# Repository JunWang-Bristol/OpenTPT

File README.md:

# OpenTPT - Open Triple Pulse Test

OpenTPT is an open-source Triple Pulse Test (TPT) platform for magnetic characterization of core loss and inductance in power magnetics and power electronics applications.

**📄 Paper:** [Triple Pulse Test (TPT) for Characterizing Magnetic Components](https://research-information.bris.ac.uk/en/publications/triple-pulse-test-tpt-for-characterizing-power-loss-in-magnetic-c)

---

## 📋 Overview

The **Triple Pulse Test (TPT)** is a discontinuous excitation method for characterizing power losses and inductance in magnetic components. Unlike traditional continuous excitation methods, TPT uses a series of precisely timed pulses to achieve steady-state magnetic conditions rapidly.

### Discontinuous Procedure

| Pulse | Purpose | Description |
|-------|---------|-------------|
| **First Pulse** | Establish DC bias | No additional DC bias source needed |
| **Second Pulse(s)** | Stabilizing | Allow transients to settle |
| **Third Pulse** | Target cycle | Steady-state measurement |

---

## ✨ Features

- ⚡ **Rapid Testing** – Short transition time (100–500 µs), ideal for end-of-line and 100% testing
- 🔄 **Bidirectional Current Flow** – Emulates practical B-H loop in PWM converters
- 💰 **Low Cost** – Reduced setup requirements compared to traditional methods
- 🌡️ **Constant Temperature** – Negligible heat generated during testing
- 📊 **DC Bias Capability** – Characterize saturation curves with built-in DC bias support
- 🖥️ **Web Dashboard** – Real-time visualization with Dash frontend

---

## 🔧 Hardware Setup

### Testing Circuit (Half-Bridge)

### Example Equipment

| Component | Supported Models | Description |
|-----------|-----------------|-------------|
| **Power Supply** | BK Precision 9129B | Dual-channel supply (V+ and V-) |
| **Oscilloscope** | PicoScope 2408B | Captures voltage/current waveforms |
| **Control Board** | NUCLEO-H503RB, ST2402 | Generates PWM pulses for H-bridge |
| **Current Probe** | 100 mV/A (recommended) | Measures inductor current, > 20 MHz |
| **Voltage Probes** | 10:1 passive probes | Input/output voltage measurement |

> 💡 **Use Your Existing Equipment!**
>
> TPT is designed to work with lab equipment you likely already have. The modular architecture uses a **`hardware_configuration.json`** file to specify your power supply, oscilloscope, and control board. Simply configure the JSON with your device names and COM ports—no need to purchase specific models listed above.
>
> Adding support for new hardware is straightforward: implement the interfaces in `power_supply.py`, `oscilloscope.py`, or `board.py`.

---

## 🚀 Quick Start

### Prerequisites

- Python 3.8 or higher
- Hardware setup (power supply, oscilloscope, control board) connected to your PC

### Installation

1. **Clone the repository**
   ```bash
   git clone https://github.com/JunWang-Bristol/OpenTPT.git
   cd OpenTPT
   ```

2. **Create a virtual environment** (recommended)
   ```bash
   python -m venv venv
   
   # Windows
   venv\Scripts\activate
   
   # Linux/macOS
   source venv/bin/activate
   ```

3. **Install dependencies**
   ```bash
   pip install -r requirements.txt
   ```

4. **Configure hardware** – Copy and edit the hardware configuration:
   ```bash
   cp hardware_configuration_template.json hardware_configuration.json
   ```
   
   Edit `hardware_configuration.json` with your port assignments:
   ```json
   {
       "power_supply": "BK9129B",
       "power_supply_port": "COM3",
       "oscilloscope": "PicoScope2408B",
       "oscilloscope_port": "COM5",
       "board": "NUCLEO-H503RB",
       "board_port": "COM6",
       "input_voltage_probe_scale": 10,
       "output_voltage_probe_scale": 10,
       "current_probe_scale": 10
   }
   ```

5. **Verify your setup** – Run tests to ensure everything is configured correctly:
   ```bash
   cd tests
   python -m pytest .
   ```
   
   Or run individual hardware tests:
   ```bash
   python board_tests.py
   python oscilloscope_tests.py
   python power_supply_tests.py
   ```

### Running Your First Measurement

#### Using Python API

```python
from src.tpt import InductanceMeasurement, CoreLossesMeasurement

# Initialize the measurement system
meas = InductanceMeasurement(
    power_supply='BK9129B',
    oscilloscope='PicoScope2408B',
    board='NUCLEO-H503RB',
    power_supply_port='COM3',
    oscilloscope_port='USB',
    board_port='COM6',
    current_probe_scale=10   # 100 mV/A probe (10 A/V)
)

# Demagnetize the core before measurement
meas.demagnetize()

# Create test parameters for frequency sweep
params = meas.create_balanced_pulse_train(
    voltage=10,       # Voltage amplitude (V)
    frequency=100000, # Frequency (Hz)
    num_pulses=4      # Number of pulse pairs
)

# Run measurement...
# (See examples in documentation)

# Clean up after measurement
meas.demagnetize()
```

#### Using Web Dashboard

1. Navigate to the frontend directory:
   ```bash
   cd src/frontend
   ```

2. Run the dashboard:
   ```bash
   python frontend.py
   ```

3. Open your browser to `http://127.0.0.1:8050`

---

## 📁 Project Structure

```
OpenTPT/
├── src/
│   ├── tpt.py                 # Main measurement classes (InductanceMeasurement, CoreLossesMeasurement)
│   ├── post_processor.py      # Waveform analysis and loop extraction
│   ├── board.py               # Control board interface
│   ├── oscilloscope.py        # Oscilloscope interface
│   ├── power_supply.py        # Power supply interface
│   ├── boards/                # Board drivers
│   │   ├── NUCLEO-H503RB/     # STM32 NUCLEO board firmware
│   │   └── ST2402/            # ST2402 driver board support
│   ├── oscilloscopes/         # Oscilloscope drivers
│   │   └── PicoScope.py       # PicoScope 2408B driver
│   ├── power_supplies/        # Power supply drivers
│   │   └── BK.py              # BK Precision 9129B driver
│   └── frontend/              # Web dashboard
│       └── frontend.py        # Dash-based GUI
├── tests/                     # Unit tests
├── hardware_configuration_template.json
├── requirements.txt
└── LICENSE
```

---

## 📝 Configuration Notes

### Current Probe Scale

> ⚠️ **Important:** The `current_probe_scale` defines how to convert oscilloscope voltage readings to actual current values:
>
> `Current (A) = Oscilloscope Voltage (V) × probe_scale`
>
> `probe_scale` must be entered in **A/V** — the reciprocal of the probe's rated sensitivity
> (often printed as mV/A, V/A, or as a current-probe amplifier's "mA/mV" gain setting).

| Probe Sensitivity | Probe Scale Value |
|-------------------|-------------------|
| 100 mV/A (0.1 V/A) | `10` |
| 1 V/A | `1.0` |
| 10 mV/A (0.01 V/A) | `100` |

**Common mistake:** For a 100 mV/A probe, use `scale=10` (not 0.1). The probe outputs 0.1 V when 1 A flows, so you must *divide* by 0.1 (i.e. multiply by 10) to recover amperes. Using the raw 0.1 V/A rating directly under-reports current by 100x — if a Tektronix P6021-style current-probe amplifier is set to "10 mA/mV", that dial reading is already in A/V and can be entered as `scale=10` with no conversion.

---

## 🤝 Contributors

| Organization | Contributors |
|-------------|--------------|
| **PSMA/Würth Elektronik** | George Slama, Alfonso Martinez, Matt Wilkowski |
| **University of Bristol** | Jun Wang, Binyu Cui, Jingrong Yang |
| **University of Manchester** | Cheng Zhang |

---

## 📅 Roadmap

**🚧 OpenTPT – Project Under Construction**

Expected release: **APEC 2027**

---

## 📄 License

This project is licensed under the **BSD 4-Clause License** – see the [LICENSE](LICENSE) file for details.

Copyright © 2023, University of Bristol

---

## 📚 Citation

If you use this project in your research, please cite:

```bibtex
@inproceedings{OpenTPT,
  title={Triple Pulse Test (TPT) for characterizing power loss in magnetic components in analogous to Double Pulse Test (DPT) for power electronics devices},
  author={Wang, Jun and others},
  booktitle={IEEE Proc. Annual Conference of the IEEE Industrial Electronics Society (IECON)},
  year={2020}
}
```

---

## 📧 Contact

For questions, issues, or contributions, please:
- Open an [issue](https://github.com/JunWang-Bristol/OpenTPT/issues) on GitHub
- Contact the team at jun.wang@bristol.ac.uk

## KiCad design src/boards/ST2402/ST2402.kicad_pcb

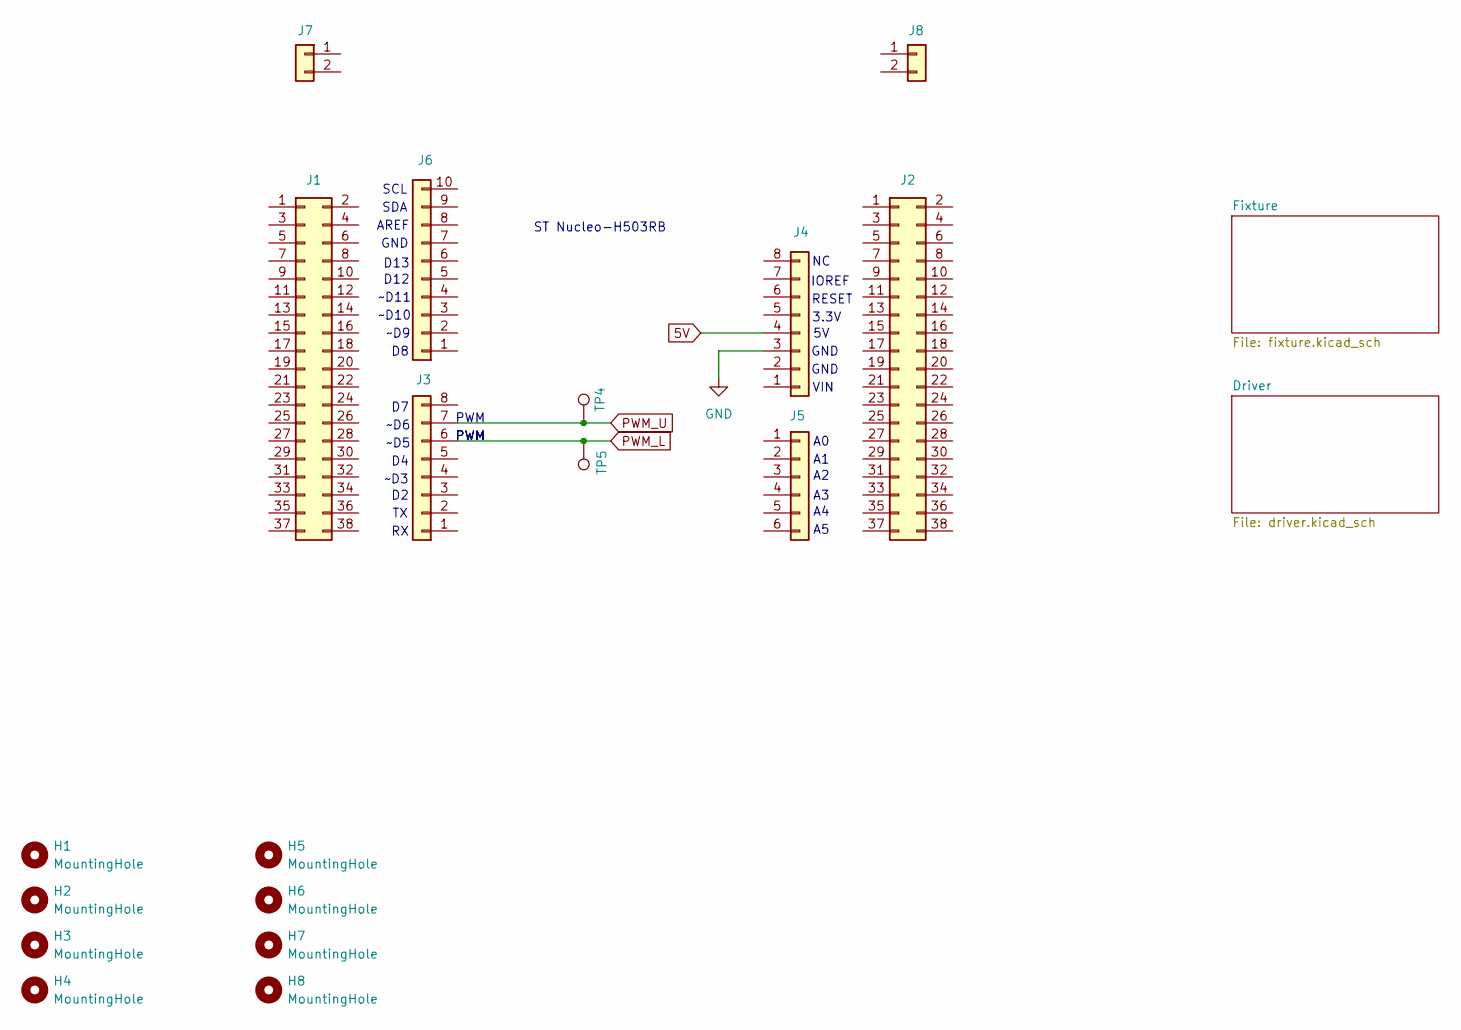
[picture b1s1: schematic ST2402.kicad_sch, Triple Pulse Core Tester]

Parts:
H1, H2, H3, H4, H5, H6, H7, H8: MountingHole; MountingHole_3.2mm_M3_DIN965
J1, J2: Conn_02x19_Odd_Even; PinHeader_2x19_P2.54mm_Vertical
J3, J4: Conn_01x08; PinHeader_1x08_P2.54mm_Vertical
J5: Conn_01x06; PinHeader_1x06_P2.54mm_Vertical
J6: Conn_01x10; PinHeader_1x10_P2.54mm_Vertical
J7, J8: Conn_01x02; PinHeader_1x02_P2.54mm_Vertical
TP4, TP5: TestPoint; TestPoint_Keystone_5010-5014_Multipurpose

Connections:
5V: J4.4
GND: J4.3; also elsewhere on the board
PWM_L: J3.6, TP5.1; also elsewhere on the board
PWM_U: J3.7, TP4.1; also elsewhere on the board

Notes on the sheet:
~D9
GND
3.3V
SCL
IOREF
SDA
D13
RESET
~D11
~D6
PWM
D12
~D5
~D3
AREF
VIN
~D10
ST Nucleo-H503RB

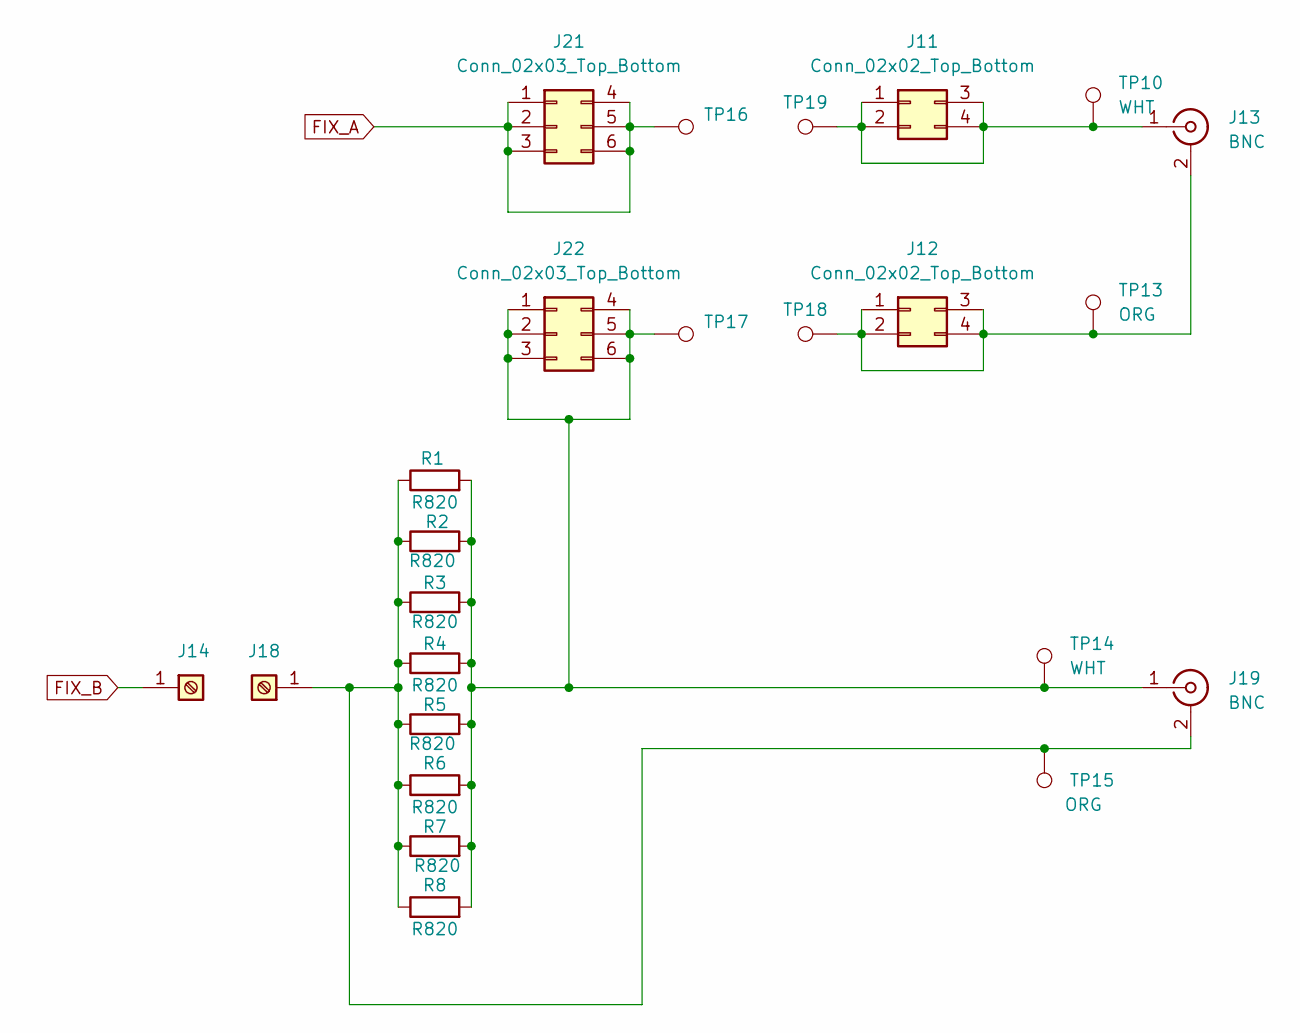
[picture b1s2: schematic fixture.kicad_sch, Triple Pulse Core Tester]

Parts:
J11, J12: Conn_02x02_Top_Bottom; PinSocket_2x02_P2.54mm_Vertical
J13, J19: BNC; BNC_Amphenol_B6252HB-NPP3G-50_Horizontal
J14, J18: Screw_Terminal_01x01; TestPoint_Plated_Hole_D2.0mm
J21, J22: Conn_02x03_Top_Bottom; PinHeader_2x03_P2.54mm_Vertical
R1, R2, R3, R4, R5, R6, R7, R8: R820; R_0805_2012Metric
TP10, TP14: WHT; TestPoint_THTPad_D2.0mm_Drill1.0mm
TP13, TP15: ORG; TestPoint_THTPad_D2.0mm_Drill1.0mm
TP16, TP17, TP18, TP19: TestPoint; TestPoint_Plated_Hole_D5.0mm

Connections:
FIX_A: J21.1, J21.2, J21.3, J21.4, J21.5, J21.6, TP16.1; also elsewhere on the board
FIX_B: J14.1; also elsewhere on the board
unnamed: J11.1, J11.2, J11.3, J11.4, J13.1 (In), TP10.1, TP19.1
unnamed: J12.1, J12.2, J12.3, J12.4, J13.2 (Ext), TP13.1, TP18.1
unnamed: J18.1, J19.2 (Ext), R1.1, R2.1, R3.1, R4.1, R5.1, R6.1, R7.1, R8.1, TP15.1
unnamed 11: J19.1 (In), J22.1, J22.2, J22.3, J22.4, J22.5, J22.6, R1.2, R2.2, R3.2, R4.2, R5.2, R6.2, R7.2, R8.2, TP14.1, TP17.1; also elsewhere on the board

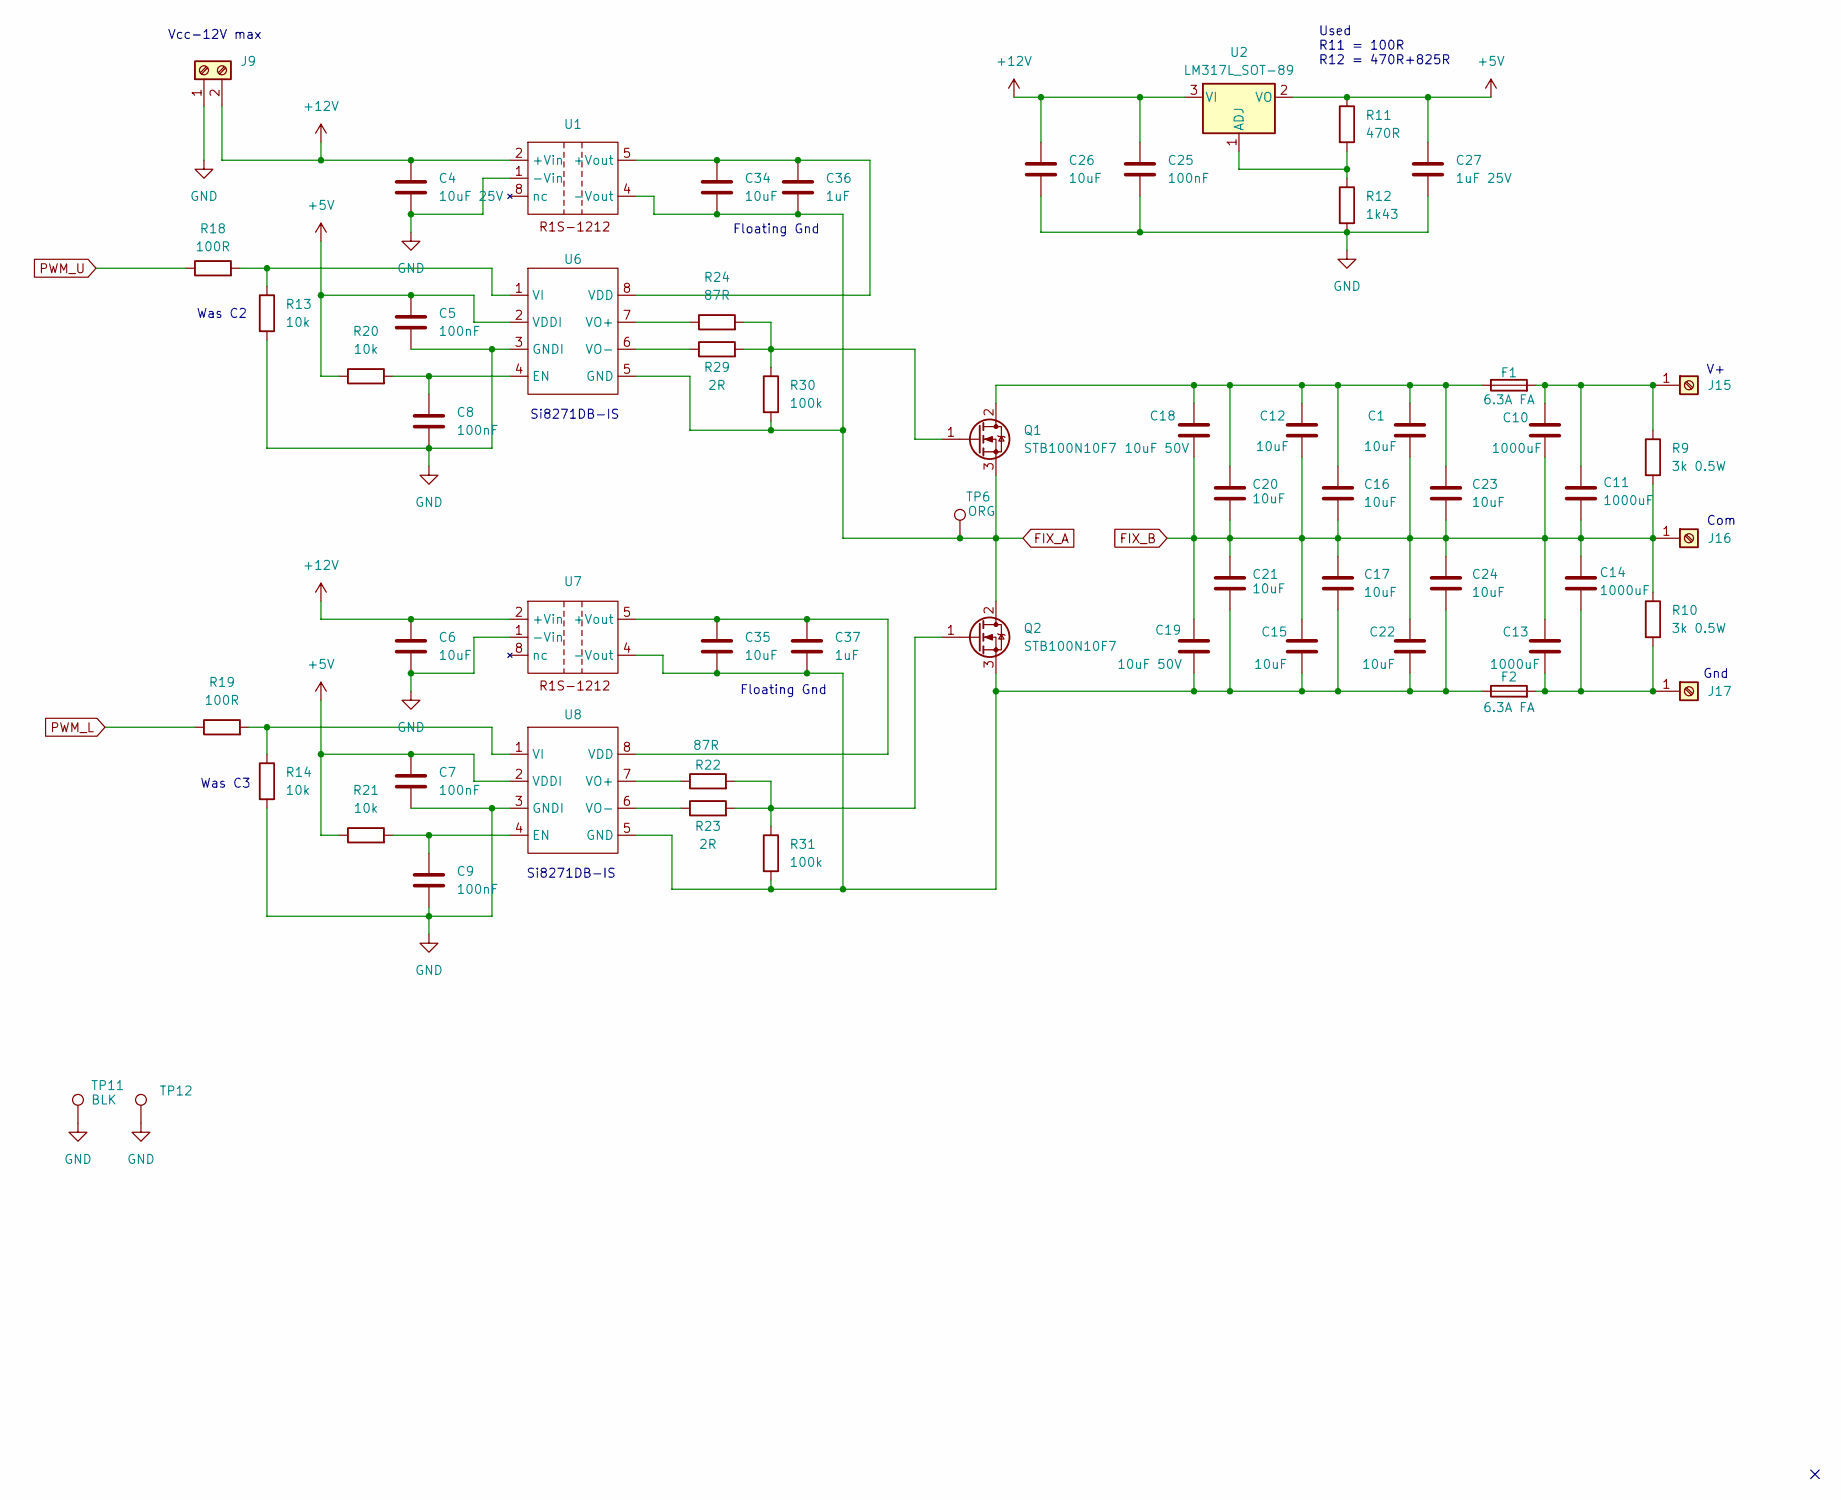
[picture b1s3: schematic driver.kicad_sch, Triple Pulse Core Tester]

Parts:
C1, C12, C15, C16, C17, C20, C21, C22, C23, C24: 10uF; C_1210_3225Metric
C4: 10uF 25V; C_0805_2012Metric
C5, C7, C8, C9, C25: 100nF; C_0805_2012Metric
C6, C26, C34, C35: 10uF; C_0805_2012Metric
C10, C11, C13, C14: 1000uF; CP_Radial_D30.0mm_P10.00mm_SnapIn
C18, C19: 10uF 50V; C_1210_3225Metric
C27: 1uF 25V; C_0805_2012Metric
C36, C37: 1uF; C_0805_2012Metric
F1, F2: 6.3A FA; Fuseholder_TR5_Littelfuse_No560_No460
J9: Screw_Terminal_01x02; TerminalBlock_bornier-2_P5.08mm
J15, J16, J17: Screw_Terminal_01x01; Banana_4mm_pcb
Q1, Q2: STB100N10F7; TO-220-3_Vertical
R9, R10: 3k 0.5W; R_Axial_DIN0309_L9.0mm_D3.2mm_P15.24mm_Horizontal
R11: 470R; R_0805_2012Metric
R12: 1k43; R_0805_2012Metric
R13, R14, R20, R21: 10k; R_0805_2012Metric
R18, R19: 100R; R_0805_2012Metric
R22, R24: 87R; R_0805_2012Metric
R23, R29: 2R; R_0805_2012Metric
R30, R31: 100k; R_0805_2012Metric
TP6: ORG; TestPoint_Keystone_5010-5014_Multipurpose
TP11: BLK; TestPoint_Keystone_5010-5014_Multipurpose
TP12: TestPoint; TestPoint_Keystone_5010-5014_Multipurpose
U1, U7: 5_pin_single_smd
U2: LM317L_SOT-89; SOT-89-3
U6, U8: SOIC-8_3.9x4.9mm_P1.27mm

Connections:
+5V: C5.1, C7.1, C27.1, R11.1, R20.1, R21.1, U2.2 (VO), U6.2 (VDDI), U8.2 (VDDI)
+12V: C4.1, C6.1, C25.1, C26.1, J9.2, U1.2 (+Vin), U2.3 (VI), U7.2 (+Vin)
FIX_A: C34.2, C36.2, Q1.3 (S), Q2.2 (D), R30.2, TP6.1, U1.4 (-Vout), U6.5 (GND); also elsewhere on the board
FIX_B: C1.2, C10.2, C11.2, C12.2, C13.1, C14.1, C15.1, C16.2, C17.1, C18.2, C19.1, C20.2, C21.1, C22.1, C23.2, C24.1, J16.1, R9.2, R10.1; also elsewhere on the board
GND: C4.2, C5.2, C6.2, C7.2, C8.2, C9.2, C25.2, C26.2, C27.2, J9.1, R12.2, R13.2, R14.2, TP11.1, TP12.1, U1.1 (-Vin), U6.3 (GNDI), U7.1 (-Vin), U8.3 (GNDI); also elsewhere on the board
unnamed: C10.1, C11.1, F1.2, J15.1, R9.1
unnamed: C13.2, C14.2, F2.2, J17.1, R10.2
unnamed: C1.1, C12.1, C16.1, C18.1, C20.1, C23.1, F1.1, Q1.2 (D)
unnamed: Q1.1 (G), R24.2, R29.2, R30.1
unnamed: Q2.1 (G), R22.2, R23.2, R31.1
unnamed: C15.2, C17.2, C19.2, C21.2, C22.2, C24.2, C35.2, C37.2, F2.1, Q2.3 (S), R31.2, U7.4 (-Vout), U8.5 (GND)
unnamed: C34.1, C36.1, U1.5 (+Vout), U6.8 (VDD)
unnamed: R11.2, R12.1, U2.1 (ADJ)
unnamed: C8.1, R20.2, U6.4 (EN)
unnamed 19: R13.1, R18.2, U6.1 (VI); also elsewhere on the board
unnamed: R24.1, U6.7 (VO+)
unnamed: R29.1, U6.6 (VO-)
unnamed: C35.1, C37.1, U7.5 (+Vout), U8.8 (VDD)
unnamed: C9.1, R21.2, U8.4 (EN)
unnamed 24: R14.1, R19.2, U8.1 (VI); also elsewhere on the board
unnamed: R22.1, U8.7 (VO+)
unnamed: R23.1, U8.6 (VO-)
PWM_L: R19.1; also elsewhere on the board
PWM_U: R18.1; also elsewhere on the board

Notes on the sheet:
Was C3
Si8271DB-IS
Was C2
Vcc-12V max
Floating Gnd
Used R11 = 100R R12 = 470R+825R
Gnd
Com

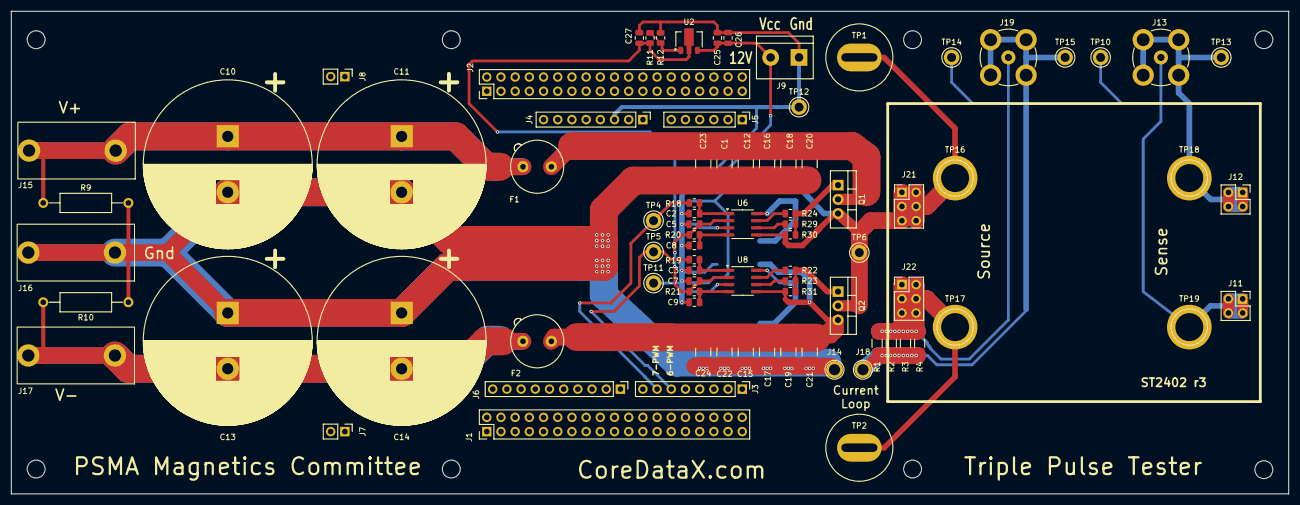
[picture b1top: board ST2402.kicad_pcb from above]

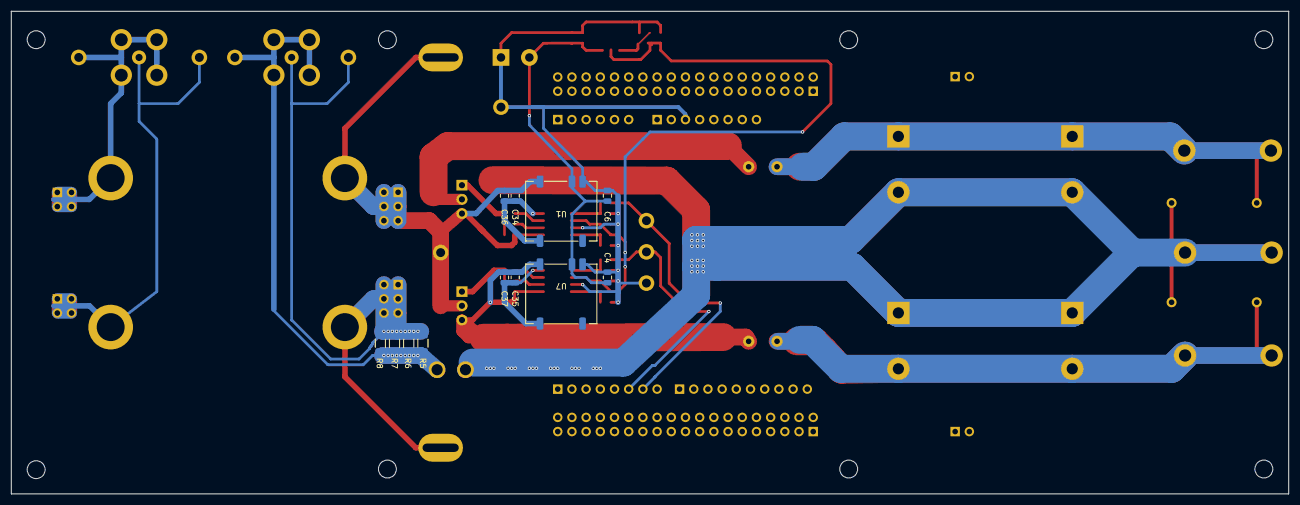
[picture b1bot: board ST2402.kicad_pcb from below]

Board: 2 copper layers, 228.6 x 86.4 mm, 105 parts (12 on the bottom side), 28 nets.

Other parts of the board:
C2, C3: 100nF; C_0805_2012Metric
TP1, TP2: TestPoint; TestPoint_Plated_Hole_D5.0mm

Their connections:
FIX_A: TP1.1; also elsewhere on the board
GND: C2.2, C3.2; also elsewhere on the board
unnamed 11: TP2.1; also elsewhere on the board
unnamed 19: C2.1; also elsewhere on the board
unnamed 24: C3.1; also elsewhere on the board

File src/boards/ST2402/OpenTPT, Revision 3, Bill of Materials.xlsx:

Index | Reference | Value | Footprint | Mfg / Part Number | Replacement Part | Qty Per Assembly | Mouser SKU (ref) | DKPN | DK, Qty Price Break | Price Each | Qty x3+10%+Break | Expan Cost | Notes
1 | U1,U7 | R1S-1212 | GS_Library:5_pin_single_smd |  |  | 2 | 919-R1S-1212 | 945-3298-ND | 1 | 7.75 | 7 | 54.25
2 | U2 | LM317L_SOT-89 | Package_TO_SOT_SMD:SOT-89-3 | LM317LCPK |  | 1 | 595-LM317LCPK | 296-26093-1-ND | 10 | 0.437 | 10 | 4.37
3 | U6,U8 | Si8271DB-IS | Package_SO:SOIC-8_3.9x4.9mm_P1.27mm | Si8271DB-IS |  | 2 | 634-Si8271DB-IS | 336-3532-5-ND | 10 | 2.677 | 10 | 26.77
4 | Q1,Q2 | STP100N10F7 | Package_TO_SOT_THT:TO-220-3_Vertical | STP100N10F7 |  | 2 | 511-STP100N10F7 | 497-13550-5-ND | 1 | 0.269 | 7 | 1.883 | Schematic calls for STB100N10F7, this is D2PAK part. PCB has TO-220 parts.
5 | C5,C7,C8,C9,C25 | 100 nF, 16 V | Capacitor_SMD:C_0805_2012Metric | 885012207098 |  | 5 | 710-885012207098 | 732-8080-1-ND | 10 | 0.038 | 20 | 0.76
6 | C27,C36,C37 | 1 uF, 25V | Capacitor_SMD:C_0805_2012Metric | 885012207103 |  | 3 | 710-85012207103 | 732-7678-1-ND | 10 | 0.169 | 10 | 1.69
7 | C4, C6,C26,C34,C35 | 10 uF, 25V | Capacitor_SMD:C_0805_2012Metric | GRM21BR61H106KE43L |  | 5 |  | 490-18663-1-ND | 10 | 0.174 | 20 | 3.48
8 | C1,C12,C15,C16,C17,C18,C19,C20,C21,C22,C23,C24 | 10 uF, 50 V, X7R | Capacitor_SMD:C_1210_3225Metric | Wurth 885012209073 | CL32B106KBJNNNE | 12 | 710-885012209073 | 1276-3387-1-ND | 10 | 0.35 | 40 | 14
9 | C10,C11,C13,C14 | 1000 uF, 200 V | Capacitor_THT:CP_Radial_D30.0mm_P10.00mm_SnapIn | Wurth 861141085021 |  | 4 | 710-861141085021 | 732-11901-ND | 10 | 5.14 | 20 | 102.8
10 | R23,R29 | 2 ohm | Resistor_SMD:R_0805_2012Metric | CRCW08052R00FKEA |  | 2 | 71-RCW08052R00FKEA | 541-2.00CCCT-ND | 10 | 0.05 | 10 | 0.5
11 | R22,R24 | 87 ohm, 1% | Resistor_SMD:R_0805_2012Metric |  | ERJ-6ENF86R6V | 2 |  | P86.6CCT-ND | 10 | 0.052 | 10 | 0.52 | ls off
12 | R18,R19 | 100 ohm, 1% | Resistor_SMD:R_0805_2012Metric |  | ERJ-P06F1000V | 2 |  | P16057CT-ND | 10 | 0.084 | 10 | 0.84 | dead time
13 | R11 | 470 ohm | Resistor_SMD:R_0805_2012Metric | RC0805FR-07470RL |  | 1 | 603-RC0805FR-07470RL | 311-470CRCT-ND | 10 | 0.012 | 10 | 0.12
14 | R1,R2,R3,R4,R5,R6,R7,R8 | R820, 1%, 1206, 100ppm | Resistor_SMD:R_1206_3216Metric | RCWE1206R820FKEA |  | 8 | 71-RCWE1206R820FKEA | RCWE.82ECT-ND | 10 | 0.179 | 30 | 5.37
15 | (Alt for R1,R2,R3,R4,R5,R6,R7,R8) | R820, 1%, 1206, 200ppm | Resistor_SMD:R_1206_3216Metric | ERJ-8BQFR82V |  | 8 | 667-ERJ-8BQFR82V
16 | R12 | 1.43k ohm | Resistor_SMD:R_0805_2012Metric |  | CRCW08051K43FKEA | 1 |  | 541-1.43KCCT-ND | 10 | 0.041 | 10 | 0.41
17 | R9,R10 | 3k 0.5W | Resistor_THT:R_Axial_DIN0309_L9.0mm_D3.2mm_P15.24mm_Horizontal | RSF100JB-73-3K |  | 2 | 603-RSF100JB-73-3K | 3.0KW-1-ND | 10 | 0.119 | 10 | 1.19 | Part specs are larger than PCB footprint, but values are correct. Float part fo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
18 | R13,R14,R20,R21 | 10k ohm, 1% | Resistor_SMD:R_0805_2012Metric |  | ERJ-6ENF1002V | 4 |  | P10.0KCCT-ND | 10 | 0.052 | 20 | 1.04 | hs off, enable pins
19 | R30,R31 | 100k ohm | Resistor_SMD:R_0805_2012Metric | RC0805FR-07100KL |  | 2 | 603-RC0805FR-07100KL | 311-100KCRCT-ND | 10 | 0.01 | 10 | 0.1
20 | F1,F2 | 6.3A FA | Fuse:Fuseholder_TR5_Littelfuse_No560_No460 | Littelfuse 37316300410 |  | 2 | 576-37316300410 | WK3066BK-ND | 10 | 1.27 | 10 | 12.7
21 | (Also for F1, F2) | Fuse holder |  | Littelfuse #560, 6.3A | 56000001319 | 2 | 576-56000001319 | WK0001-ND | 10 | 0.89 | 10 | 8.9
24 | J3,J4,J5,J6 | Arduino Headers |  | Adafruit 85 |  | 1 | 485-85 | 1528-1074-ND | 1 | 1.95 | 4 | 7.8
25 | J21,J22 | Conn_02x03_Top_Bottom | Connector_PinHeader_2.54mm:PinHeader_2x03_P2.54mm_Vertical | Samtec SSQ10301GD |  | 2 | 200-SSQ10301GD | SAM1179-03-ND | 1 | 1.255 | 7 | 8.785 | Schematic/layout specify pin header, but BOM part is socket. Photo shows socket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
26 | J11,J12 | Conn_02x02_Top_Bottom | Connector_PinSocket_2.54mm:PinSocket_2x02_P2.54mm_Vertical | Samtec SSQ10203FD | SSQ-102-01-L-D | 2 | 200-SSQ10203FD | SAM11905-ND | 1 | 1.41 | 7 | 9.87 | Specified part is custom order. Replacement has 2.64 mm tail vs 10.00 mm
27 | J9 | Screw_Terminal_01x02 | TerminalBlock:TerminalBlock_bornier-2_P5.08mm | TB006-508-02BE |  | 1 | 490-TB006-508-02BE | 102-6191-ND | 10 | 0.389 | 10 | 3.89
28 | J15 | Banana Jack, Red | Library:Banana_4mm_pcb |  | 973582101 | 1 |  | 973582101-ND | 1 | 3.39 | 4 | 13.56 | Footprint calls for socket with 15 mm pitch. Standard parts are either 10 mm or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
29 | J16 | Banana Jack, Blue | Library:Banana_4mm_pcb |  | 105-0760-001 | 1 |  | J115-ND | 1 | 1.46 | 4 | 5.84
30 | J17 | Banana Jack, Black | Library:Banana_4mm_pcb |  | 973582100 | 1 |  | 973582100-ND | 1 | 3.39 | 4 | 13.56
31 | J13,J19 | BNC | Connector_Coaxial:BNC_TEConnectivity_1478204_Vertical | TE 1478204 (obsolete) | Amp RF 112404 | 2 |  | ACX1051-ND | 10 | 2.94 | 10 | 29.4
32 | TP16,TP18 | Binding Post, Red | TestPoint:TestPoint_Plated_Hole_D5.0mm | BU-P3760-6 |  | 2 | 548-BU-P3760-6 | 314-1496-ND | 1 | 5.33 | 7 | 37.31
33 | TP17,TP19 | Binding Post, Black | TestPoint:TestPoint_Plated_Hole_D5.0mm | BU-P3760-0 |  | 2 | 548-BU-P3760-0 | 314-1492-ND | 1 | 6.06 | 7 | 42.42
34 | TP4,TP5,TP12 | Clip loop, YEL | TestPoint:TestPoint_Keystone_5010-5014_Multipurpose | Keystone 5004 |  | 3 | 534-5004 | 36-5004-ND | 10 | 0.256 | 10 | 2.56
35 | TP6,TP13,TP15 | Clip loop, ORG | TestPoint:TestPoint_Keystone_5010-5014_Multipurpose | Keystone 5003 |  | 3 | 534-5003 | 36-5003-ND | 10 | 0.256 | 10 | 2.56
36 | TP10,TP14 | Clip loop, WHITE | TestPoint:TestPoint_Keystone_5010-5014_Multipurpose | Keystone 5002 |  | 2 | 534-5002 | 36-5002-ND | 10 | 0.203 | 10 | 2.03
37 | TP11 | Clip loop, BLACK | TestPoint:TestPoint_Keystone_5010-5014_Multipurpose | Keystone 5001 |  | 1 | 534-5001 | 36-5001-ND | 10 | 0.202 | 10 | 2.02
 |  |  |  |  |  |  |  |  |  |  | Total Cost: | 423.298

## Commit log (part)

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2025-01-02 Upload organized code for data processing
    Upload the MATLAB code to process the data generated from TPT systems.
2025-01-13 Update comments for data processing code
2025-01-21 Created new branch, with new folder architecture
2025-01-21 Added first version of SCPI server
2025-02-24 Added some SCPI commands to TPT board
2025-02-25 Added commands for running trains of pulses in the board
2025-02-25 Implemented method for reading from Picoscope
2025-02-25 Add files via upload
    ST2402 r1 files
2025-02-25 Renamed board to ST2402
2025-02-25 Set granularity to half pulse
2025-02-26 Added temptative support for PS3 and PS6
2025-02-26 Initial first mock up of TPT
2025-02-26 Added missing osc to facgtory
2025-02-26 Added method to calculate test parameters
2025-02-27 Added exception for unknown oscilloscope
2025-02-27 Fixed channel names
2025-02-27 Change ps6000a to 6000
2025-02-27 Added timeout in oscilloscope
2025-02-28 Added series and parallel mode to PSUs
2025-02-28 Added configuration by file
2025-03-01 Added method to preconfigure skew in oscilloscope
2025-03-03 Dummy power suppy added. Method for calculating core losses added
2025-03-06 Some fixes for Pico6000
2025-03-06 Fixed oscillocope tests
2025-03-07 Fixed voltage loop
2025-03-07 Extracted mean value from pulses
2025-03-07 Fixed aDC count in Pico6000
2025-03-07 Debug added
2025-03-10 Added basic frontend
2025-03-10 Added status label to GUI
2025-03-13 Added probe scaling
2025-03-15 Live change from workshop
2025-03-20 Changes from the demo
2025-03-27 Separated voltages into positive and negative, and added adjustment for both separately
2025-03-27 Disabled power supply after test ends
2025-04-08 deleted local file
2025-07-08 Added delay between positive and negative pulses
2025-07-08 Added separated pulses
2025-08-22 Added post processing
2025-08-26 Put back dc_bias_period
2025-11-11 Update expected release time to Spring 2026
2026-01-20 Added untested PMBus integration
2026-01-20 Revert "Update expected release time to Spring 2026"
    This reverts commit 2349e430e09afb3095664301f5ecd4f1a9f3f0cf.
2026-01-20 Revert "Added untested PMBus integration"
    This reverts commit 0f5cf9eb41e18a78c24ba299d12d52899623f2a6.
2026-01-20 Update expected release time to APEC 2026
2026-02-03 First version of inductance and core losses, with the help of Claude
2026-02-16 Added the open-loop pulsetrain function with documentation. Corrected the two PWM pins to pull-down
2026-02-16 Updated pcb files
    Added r2 and r3 gerbers and updated KiCad file (r3)
2026-02-17 Updated tpt-scpi.c to force two PWM pins LOW after a TPT run.
2026-02-17 Updated documentation for ver2 ST2402
2026-02-24 Revert "Updated tpt-scpi.c to force two PWM pins LOW after a TPT run."
    This reverts commit 9ae1180b8c690a1077719c36808f065f06aa5e84.
2026-02-24 LOW reset for both pulse outputs in tpt-scpi.c by fixing reset_pins() to drive PB10 and PB4 low (reset bits in BSRR), instead of leaving one pin high.
    Implemented
    Added a deterministic LOW reset for both pulse outputs in tpt-scpi.c by fixing reset_pins() to drive PB10 and PB4 low (reset bits in BSRR), instead of leaving one pin high.
    Updated TPT_RunPulses so outputs are forced LOW before a run starts, before each train repetition, after each train repetition, and once again at run completion.
    Updated SCPI_Reset to also force outputs LOW and clear running state, so reset always returns the board to a safe idle state.
    Why this solves it
    The previous end-of-run state could hold whichever comp
2026-02-25 Updated tpt-scpi.c to embed a 200 ns deadtime as turn-on delay
2026-02-25 Increased deadtime to 500 ns
2026-03-02 Stripped out unused references
2026-03-05 Added R&S scope, GWinstek power supply, inductance to tpt and bascially all new tpt
2026-03-05 Change order of execution - iterate for flux first, than balance
2026-03-25 Adding Revison 3 Bill of materials
    Merged previous revision BoM with exported BoM from Revision 3 KiCAD project.
2026-04-05 Improve firmware for higher freq
2026-04-28 Fix tests for updated hardware: BK9129B PSU, PicoScope2408B, NUCLEO-H503RB firmware v0.1.0
2026-04-28 Add core loss measurement scripts for 10-turn inductor setup
2026-04-28 Fix diagnostic script scope timeout detection logic

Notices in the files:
README.md:
License: BSD 4-Clause
